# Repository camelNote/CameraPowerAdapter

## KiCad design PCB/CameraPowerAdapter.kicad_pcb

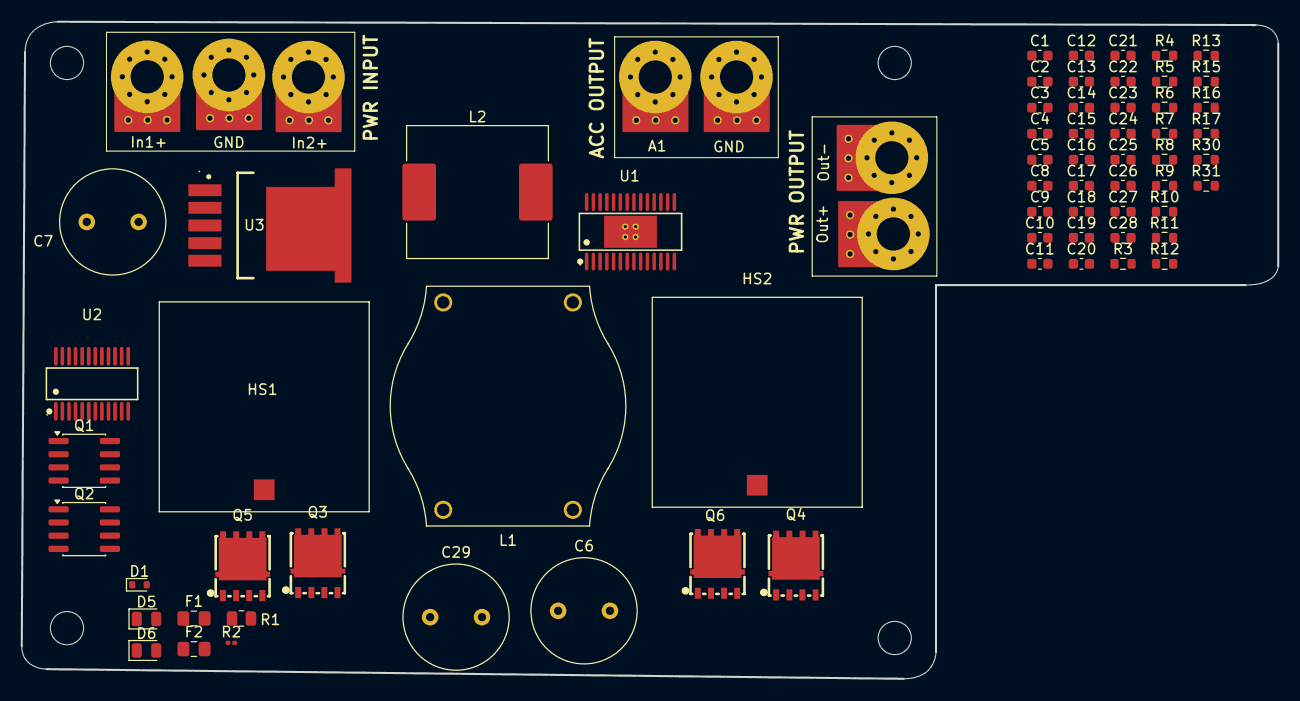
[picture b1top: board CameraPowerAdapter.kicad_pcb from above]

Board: 2 copper layers, 121.2 x 63.4 mm, 76 parts (0 on the bottom side), 38 nets, no tracks yet.

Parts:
A1: MountingHole_Pad; MG_ThermalTab_M3
C1: 100u; C_0603_1608Metric
C2, C3, C4, C5, C9, C10, C17, C18, C26, C27: 100n; C_0603_1608Metric
C6, C7: 2200u; C_Radial_D10.0mm_H12.5mm_P5.00mm
C8, C24, C28: 1u; C_0603_1608Metric
C11, C12, C13, C14, C19, C20, C21, C22: 10u; C_0603_1608Metric
C15: 4.7u; C_0603_1608Metric
C16: 470n; C_0603_1608Metric
C23: 180u; C_0603_1608Metric
C25: 15n; C_0603_1608Metric
C29: 220u; C_Radial_D10.0mm_H12.5mm_P5.00mm
D1: 1N914; D_SOD-523
D5, D6: Schottky; D_0805_2012Metric
F1, F2: Fuse; Fuse_0805_2012Metric_Pad1.15x1.40mm_HandSolder
GND: MountingHole_Pad; MG_ThermalTab_M3
GND#2: MountingHole_Pad; MG_ThermalTab_M3
H1, H2, H3, H4: MountingHole; MountingHole_3.2mm_M3
HS1, HS2: Heatsink_Pad; Heatsink_20x20x10_XSD271-294
In1+, In2+: MountingHole_Pad; MG_ThermalTab_M3
L1: 10uH; Choke_EPCOS_B82722A
L2: L; L_Sunlord_MWSA1205S-470
Out+: MountingHole_Pad; MG_ThermalTab_M3
Out-: MountingHole_Pad; MG_ThermalTab_M3
Q1, Q2: IRF7324; SOIC-8_3.9x4.9mm_P1.27mm
Q3, Q4, Q5, Q6: NCEP40T11G; DFN-8_L5.1-W5.7-P1.27-LS6.1-BL
R1: 1M; R_0805_2012Metric
R2: 1M; R_0201_0603Metric
R3, R6: 1M; R_0603_1608Metric
R4, R7: 100k; R_0603_1608Metric
R5: 2m; R_0603_1608Metric
R8: 365k; R_0603_1608Metric
R9: 56.2k; R_0603_1608Metric
R10: 499k; R_0603_1608Metric
R11: 12m; R_0603_1608Metric
R12: 226k; R_0603_1608Metric
R13: 15k; R_0603_1608Metric
R15: 110k; R_0603_1608Metric
R16: 120k; R_0603_1608Metric
R17, R30: 10k; R_0603_1608Metric
R31: 1k; R_0603_1608Metric
U1: LT8390EFE#PBF; TSSOP-28_L9.7-W4.4-P0.65-LS6.4-BL-EP
U2: LTC4417IGN#TRPBF; SSOP-24_L8.8-W4.0-P0.64-LS6.2-BL
U3: LM2596SX-5.0/NOPB; TO-263-5_L10.2-W8.9-P1.70-TL

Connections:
/AccessoryBus: A1.1 (1_1), C29.1, L2.2, U3.4 (FB)
/BG1: Q4.4 (G), U1.1 (BG1)
/BG2: Q5.4 (G), U1.28 (BG2)
/BST2: C18.2, U1.27 (BST2)
/EN/UVLO: R8.2, R9.1, U1.9 (EN/UVLO)
/FB: R16.2, R17.1, U1.19 (FB)
/G1: Q1.2 (G1), Q1.4 (G2), U2.20 (G1)
/G2: Q2.2 (G1), Q2.4 (G2), U2.18 (G2)
/INTVCC: C15.1, C28.1, R30.2, U1.8 (INTVcc), U1.22 (SYNC/SPRD)
/In1Pos: F2.1, In1+.1 (1_1)
/In2Pos: F1.1, In2+.1 (1_1)
/LSN: C27.2, L1.1, R5.2, U1.6 (LSN)
/OutPos: C19.1, C20.1, C21.1, C22.1, C23.1, C26.2, Out+.1 (1_1), R11.2, R15.1, U1.15 (ISN)
/PGOOD: R30.1, R31.1, U1.17 (PGOOD)
/PriorityInput: C4.1, C7.1, F1.2, Q1.7 (D1), Q1.8 (D1), R1.1, U2.24 (V1)
/SW1: C10.1, C27.1, D5.1 (K), HS2.1, Q4.5 (D), Q4.6 (D), Q4.7 (D), Q4.8 (D), Q4.9 (D), Q6.1 (S), Q6.2 (S), Q6.3 (S), R5.1, U1.3 (SW1), U1.5 (LSP)
/SW2: C18.1, D6.2 (A), HS1.1, L1.2, Q3.1 (S), Q3.2 (S), Q3.3 (S), Q5.5 (D), Q5.6 (D), Q5.7 (D), Q5.8 (D), Q5.9 (D), U1.26 (SW2)
/SecondaryInput: C5.1, C6.1, F2.2, Q2.7 (D1), Q2.8 (D1), R6.1, U2.23 (V2)
/TG1: Q6.4 (G), U1.4 (TG1)
/TG2: Q3.4 (G), U1.25 (TG2)
/UV1: R1.2, R4.1, U2.4 (UV1)
/UV2: R6.2, R7.1, U2.6 (UV2)
/VC: R13.1, U1.20 (Vc)
/VC_RC: C25.1, R13.2
/VOUT_REG: C24.1, C26.1, D6.1 (K), Q3.5 (D), Q3.6 (D), Q3.7 (D), Q3.8 (D), Q3.9 (D), R11.1, U1.14 (ISP), U1.24 (Vout)
/VS1: C2.1, Q1.1 (S1), Q1.3 (S2), U2.21 (VS1)
/VS2: C3.1, Q2.1 (S1), Q2.3 (S2), U2.19 (VS2)
/Vmux: C1.1, C8.1, C11.1, C12.1, C13.1, C14.1, Q1.5 (D2), Q1.6 (D2), Q2.5 (D2), Q2.6 (D2), Q6.5 (D), Q6.6 (D), Q6.7 (D), Q6.8 (D), Q6.9 (D), R2.2, R3.2, R8.1, U1.7 (Vin), U2.15 (VOUT), U3.1 (VIN)
/~VALID1: R2.1, U2.10 (~VALID1), U3.5 (~ON/OFF)
/~VALID2: R3.1, U2.11 (~VALID2)
GND: C1.2, C2.2, C3.2, C4.2, C5.2, C6.2, C7.2, C8.2, C9.2, C11.2, C12.2, C13.2, C14.2, C15.2, C16.2, C17.2, C19.2, C20.2, C21.2, C22.2, C23.2, C24.2, C25.2, C28.2, C29.2, D1.2 (A), D5.2 (A), GND.1 (1_1), GND#2.1 (1_1), Q4.1 (S), Q4.2 (S), Q4.3 (S), Q5.1 (S), Q5.2 (S), Q5.3 (S), R4.2, R7.2, R9.2, R12.2, R17.2, U1.10 (TEST), U1.29 (GND), U2.3 (HYS), U2.5 (OV1), U2.7 (OV2), U2.8 (UV3), U2.9 (OV3), U2.13 (GND), U2.17 (VS3), U2.22 (V3), U3.3 (GND), U3.6 (GND)
unnamed: D1.1 (K), L2.1, U3.2 (OUTPUT)
unnamed: R15.2, R16.1
unnamed: C16.1, R10.2, U1.11 (LOADEN), U1.12 (Vref), U1.13 (CTRL)
unnamed: C17.1, U1.16 (ISMON)
unnamed: R12.1, U1.21 (RT)
unnamed: C9.1, R10.1, U1.18 (SS)
unnamed: C10.2, U1.2 (BST1)
